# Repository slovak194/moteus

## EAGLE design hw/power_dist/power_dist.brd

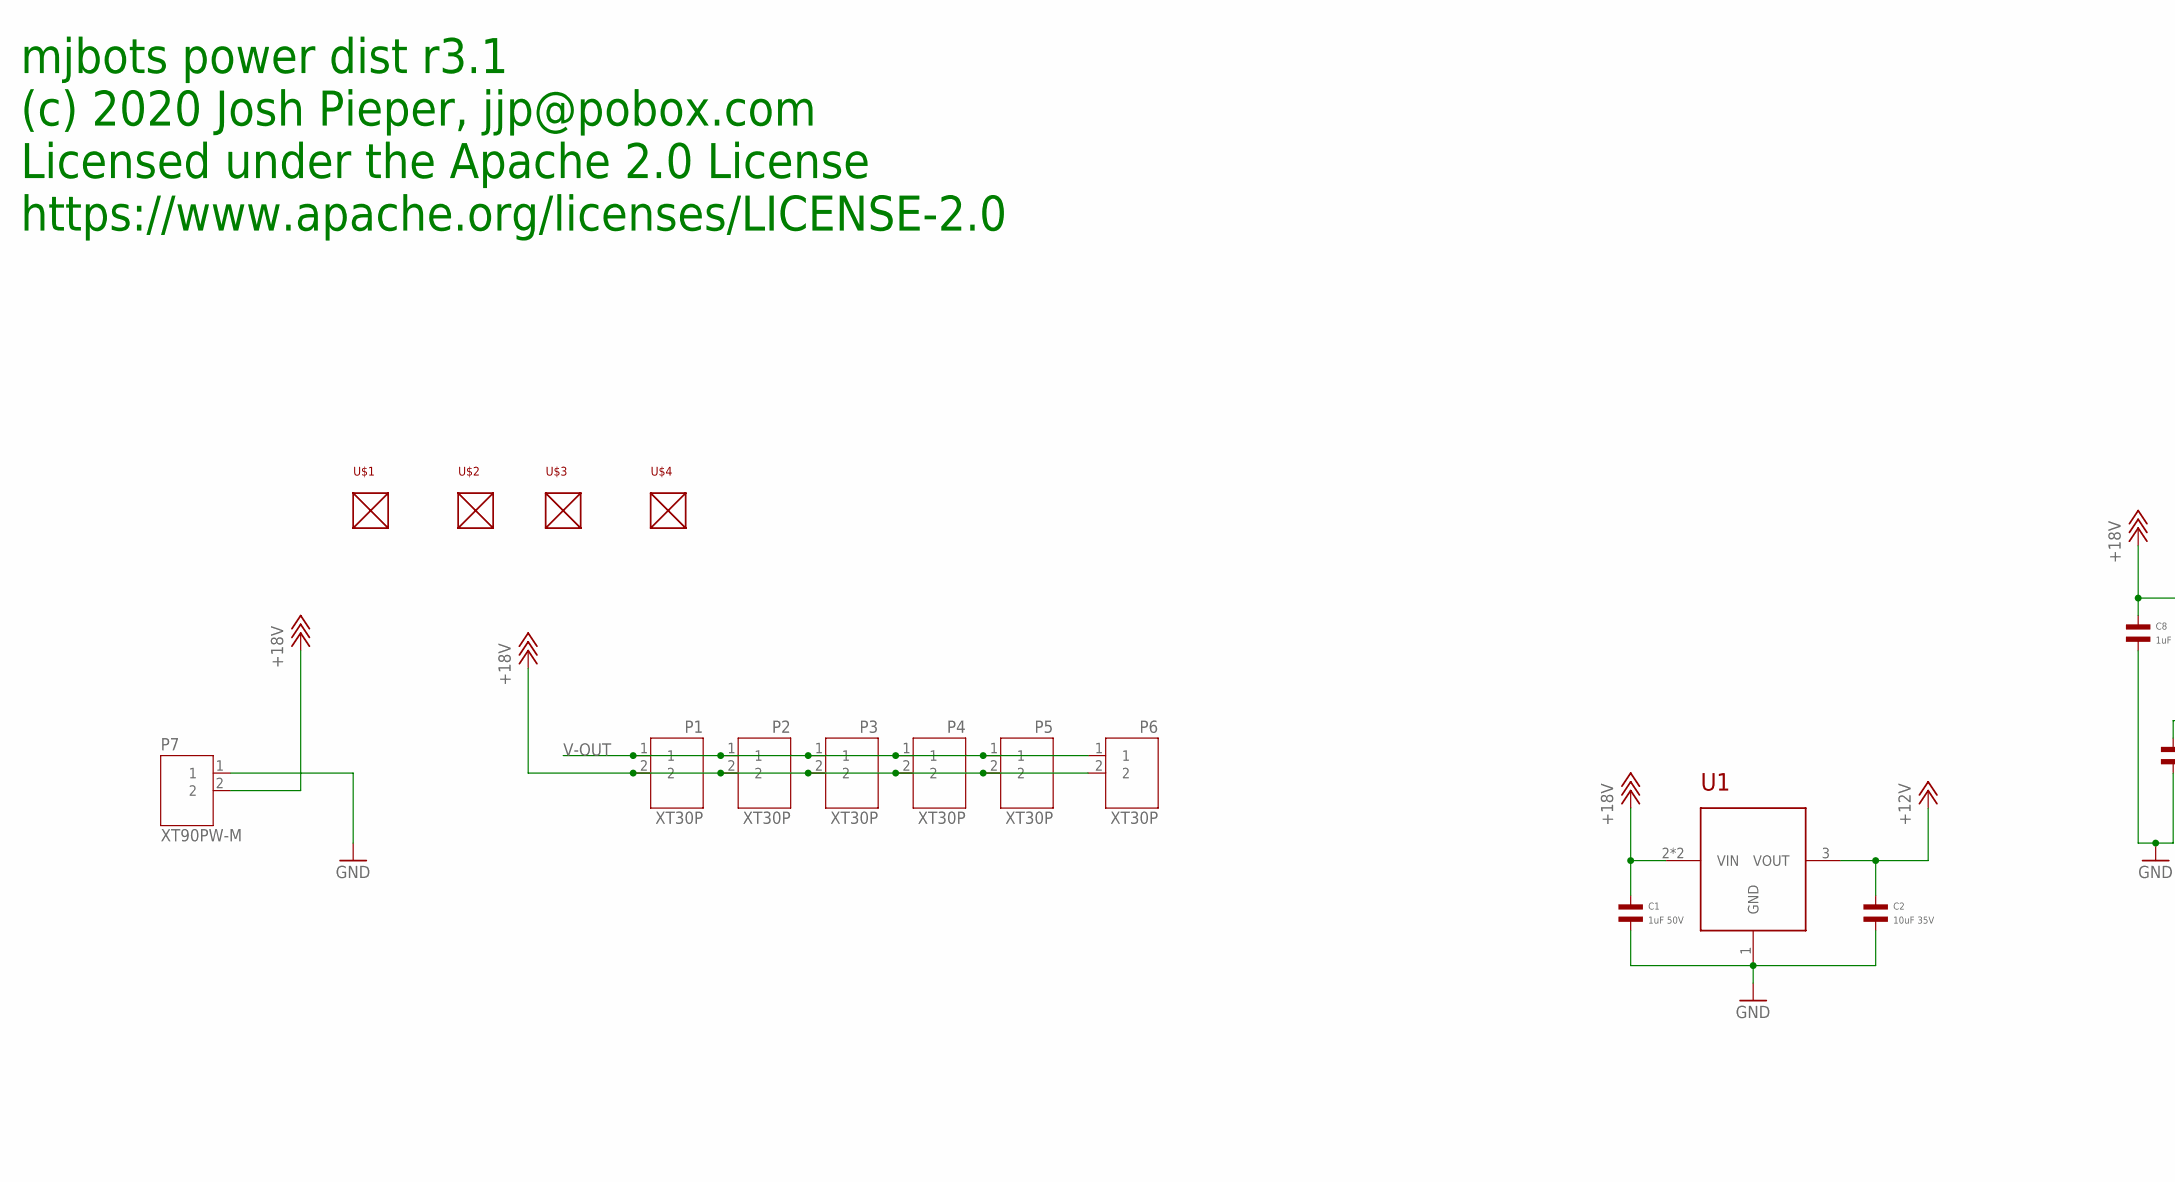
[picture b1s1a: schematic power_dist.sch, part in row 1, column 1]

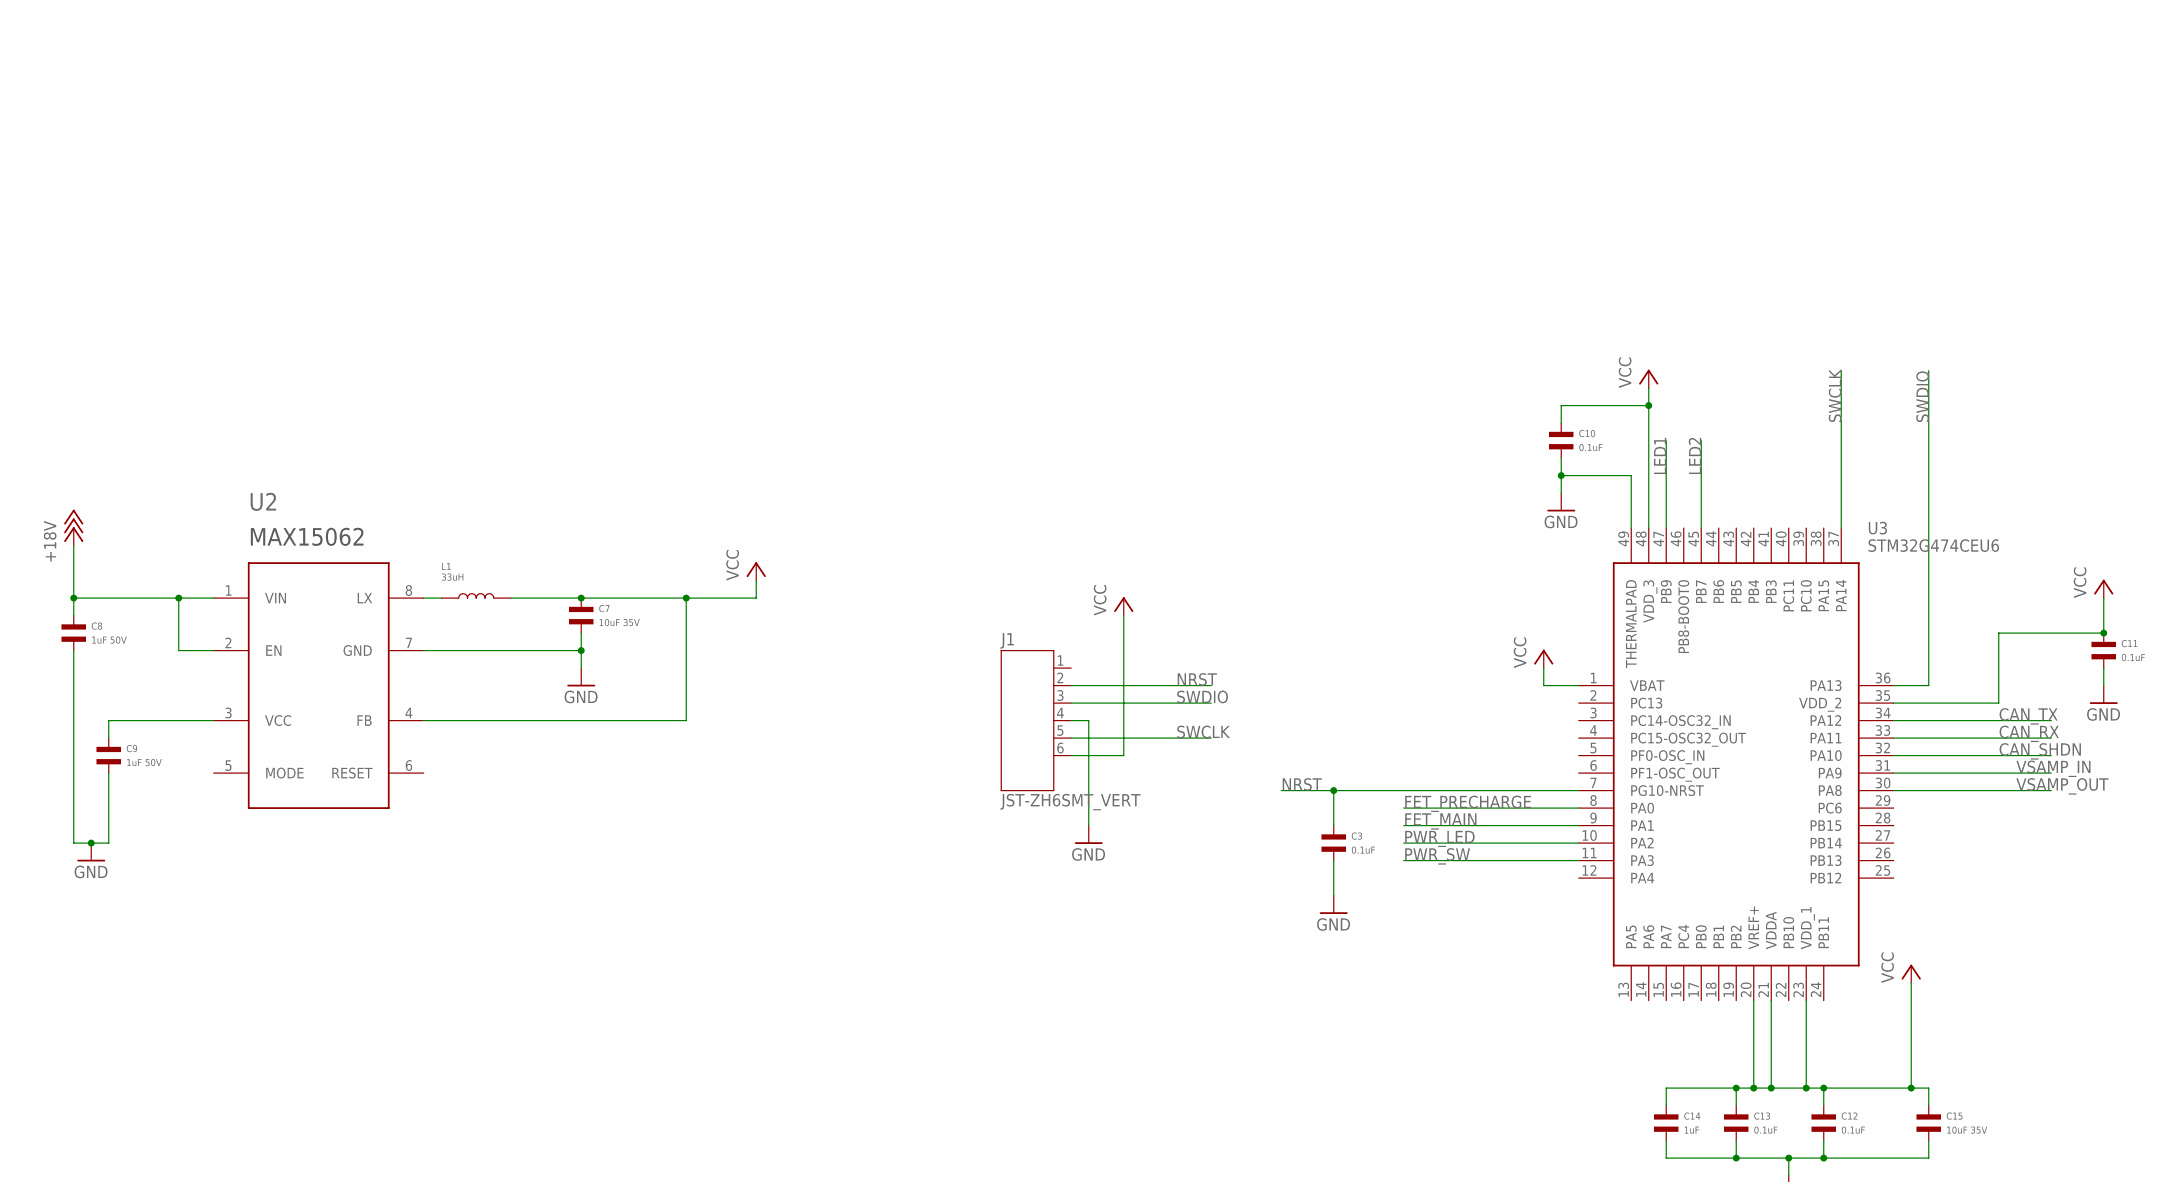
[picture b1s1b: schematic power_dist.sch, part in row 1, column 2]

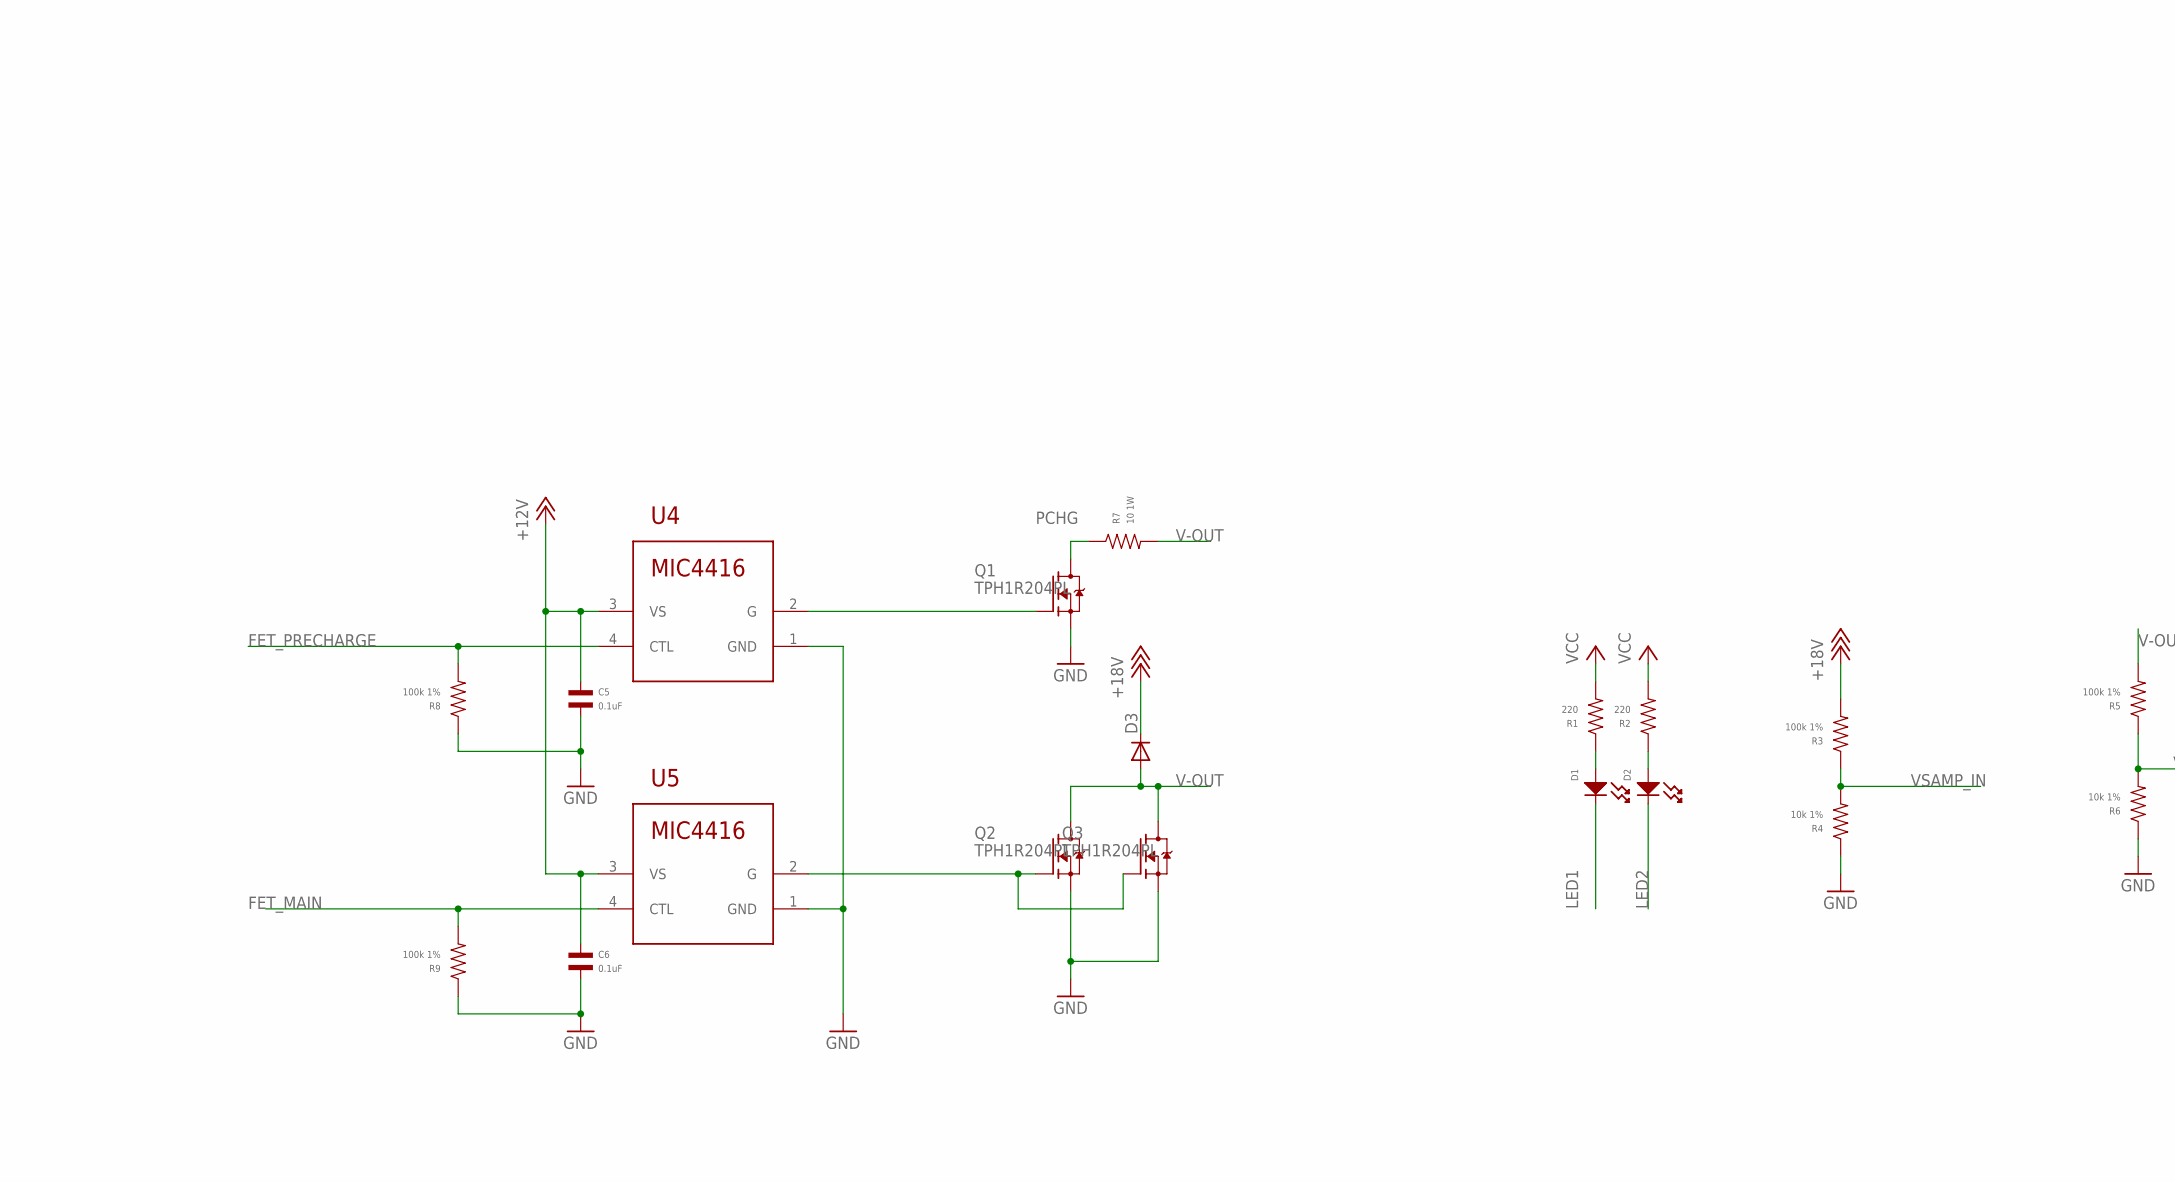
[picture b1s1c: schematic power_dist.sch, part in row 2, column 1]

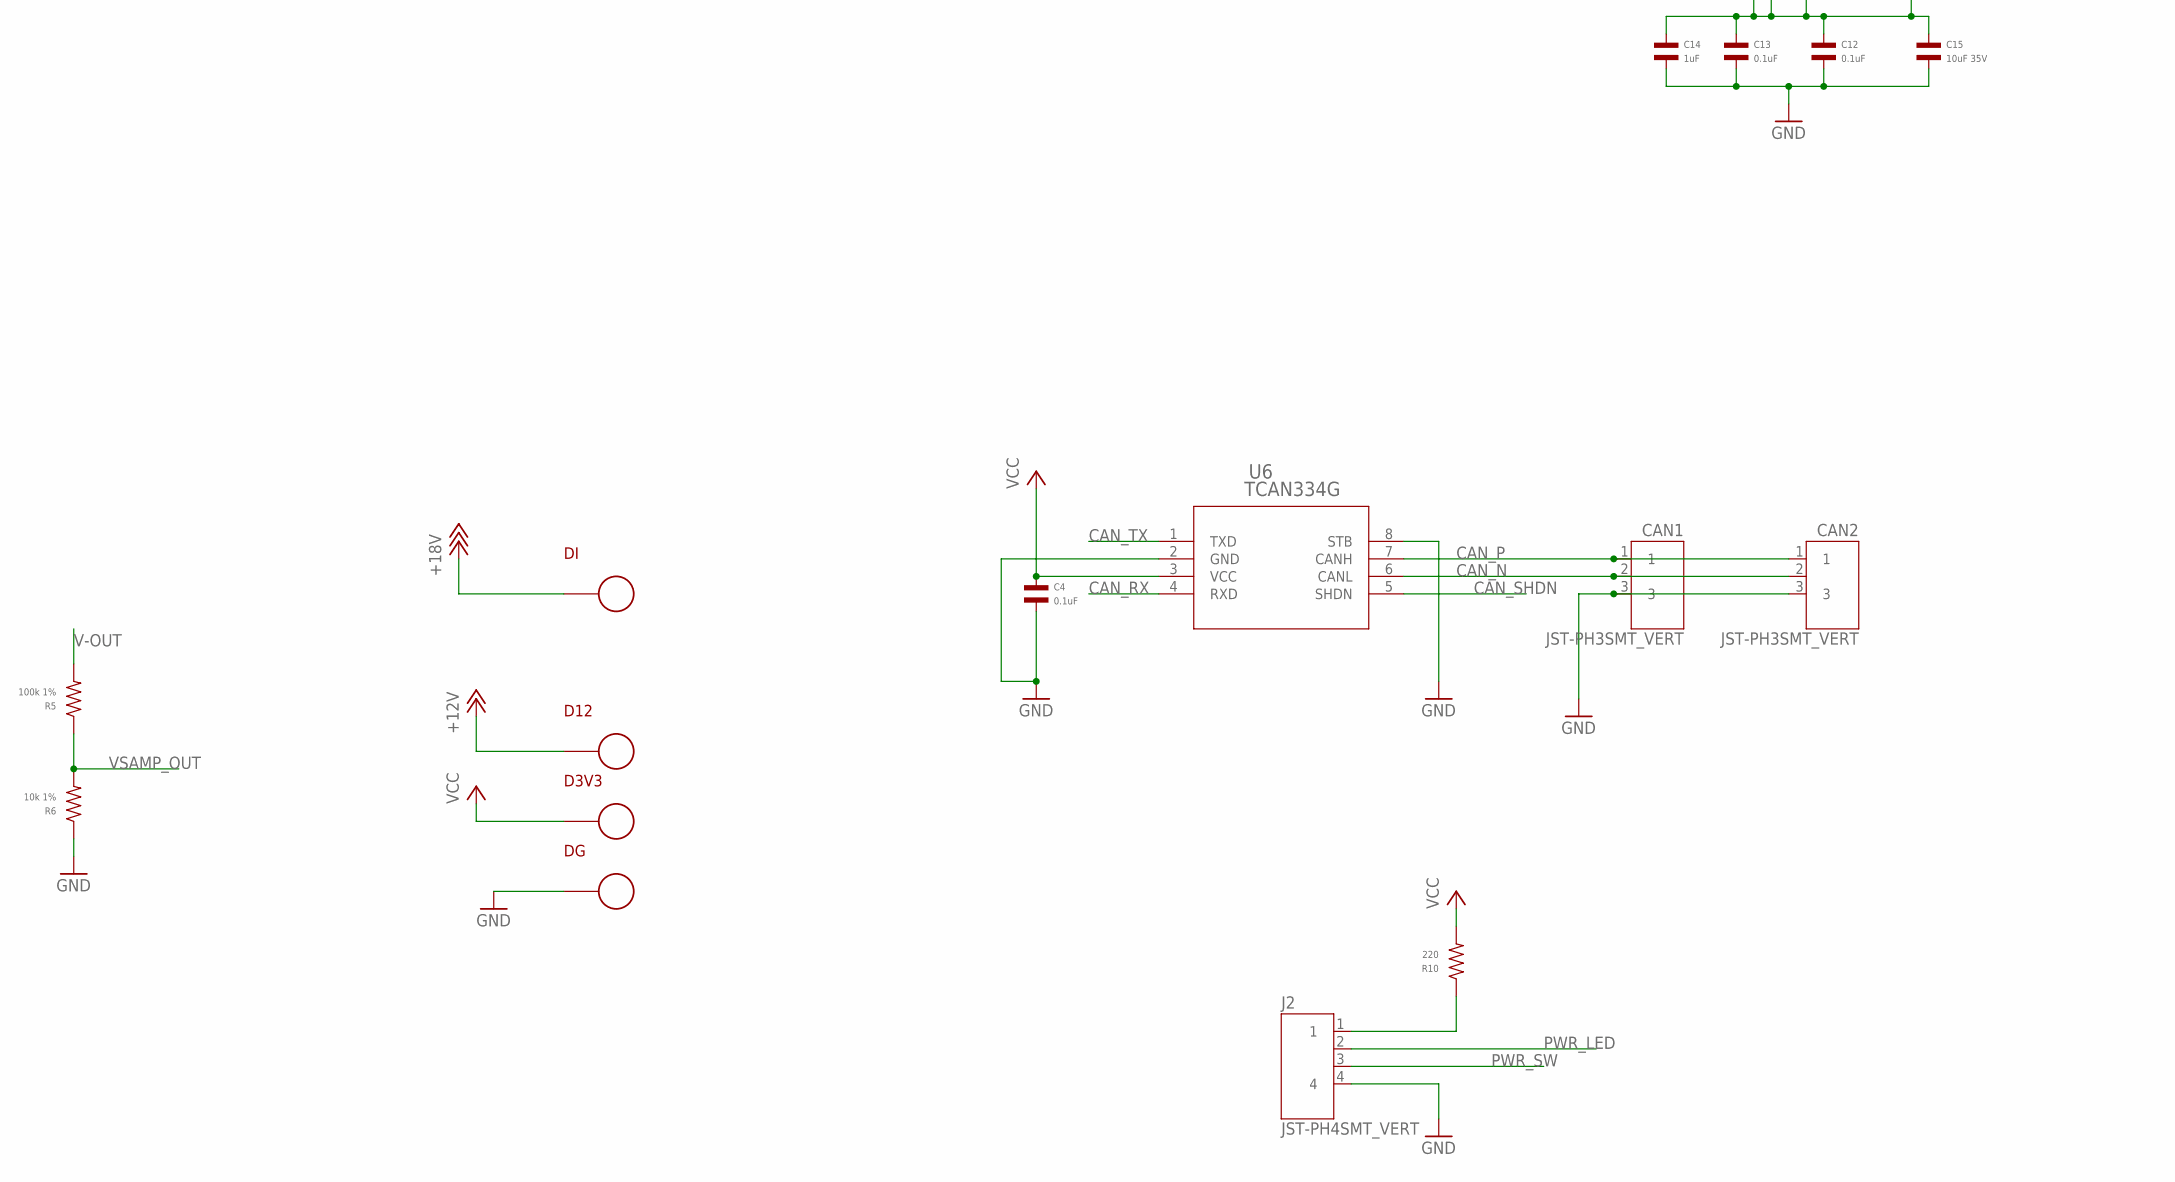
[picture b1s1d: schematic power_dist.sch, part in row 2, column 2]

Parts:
C1, C8, C9: 1uF 50V; C0603; MPN CL10A105KB8NNNC
C2, C7, C15: 10uF 35V; C1206; MPN CGA5L1X7R1V106K160AC
C3, C4, C5, C6, C10, C11, C12, C13: 0.1uF; C0402; MPN MF-CAP-0402-0.1uF
C14: 1uF; C0402; MPN MF-CAP-0402-1uF
CAN1, CAN2: JST-PH3SMT_VERT; JST_B3B_PH-SM4-TB(LF)(SN); MPN B3B-PH-SM4-TB(LF)(SN)
D1, D2: LED_SINGLE-0603; LED0603; MPN MF-LED-0603-RED
D3: DIODE-; DO-214AB; MPN SK510L-TP
D3V3, D12: PAD24AWG_PAD; 24AWG_PAD
DG: PAD24AWG_PAD; 24AWG_PAD
DI: PAD24AWG_PAD; 24AWG_PAD
J1: JST-ZH6SMT_VERT; JST_B6B-ZR-SM4-TF(LF)(SN); MPN B6B-ZR-SM4-TF(LF)(SN)
J2: JST-PH4SMT_VERT; JST_B4B_PH-SM4-TB(LF)(SN); MPN B4B-PH-SM4-TB(LF)(SN)
L1: 33uH; L1210; MPN NLFV32T-330K-EF
P1, P2, P3, P4, P5, P6: XT30P
P7: XT90PW-M
Q1, Q2, Q3: TPH1R204PL; SOP_ADVANCE; MPN TPH1R204PL,L1Q
R1, R2, R10: 220; R0603; MPN MF-RES-0603-220
R3, R5, R8, R9: 100k 1%; R0603; MPN CRCW0603100KFKEA
R4, R6: 10k 1%; R0603; MPN ERJ-3EKF1002V
R7: 10 1W; R1206; MPN HRG3216Q-10R0-D-T1
U1: ZXTR2012Z; SOT89; MPN ZXTR2012Z-13
U2: MAX150628TDFN; 8TDFN; MPN MAX15062AATA+T
U3: STM32G474CEU6; QFN50P700X700X60-49N; MPN STM32G474CEU6
U4, U5: MIC4416; SOT143
U6: TCAN334G; SOIC8; MPN LTC2875IS8
U$1, U$2, U$3, U$4: MOUNT; M2.5MOUNT

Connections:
+12V: C2.P$1, C5.P$1, C6.P$1, D12.P$1, U1.3 (VOUT), U4.3 (VS), U5.3 (VS)
+18V: C1.P$1, C8.P$1, D3.C, DI.P$1, P1.2, P2.2, P3.2, P4.2, P5.2, P6.2, P7.2, R3.P$2, U1.2 (VIN), U1.PAD (VIN), U2.1 (VIN), U2.2 (EN)
CAN_N: CAN1.2, CAN2.2, U6.6 (CANL)
CAN_P: CAN1.1, CAN2.1, U6.7 (CANH)
CAN_RX: U3.33 (PA11), U6.4 (RXD)
CAN_SHDN: U3.32 (PA10), U6.5 (SHDN)
CAN_TX: U3.34 (PA12), U6.1 (TXD)
FET_MAIN: R9.P$2, U3.9 (PA1), U5.4 (CTL)
FET_PRECHARGE: R8.P$2, U3.8 (PA0), U4.4 (CTL)
GND: C1.P$2, C2.P$2, C3.P$2, C4.P$2, C5.P$2, C6.P$2, C7.P$2, C8.P$2, C9.P$2, C10.P$2, C11.P$2, C12.P$2, C13.P$2, C14.P$2, C15.P$2, CAN1.3, CAN2.3, DG.P$1, J1.4, J2.4, P7.1, Q1.1 (S), Q1.2 (S), Q1.3 (S), Q2.1 (S), Q2.2 (S), Q2.3 (S), Q3.1 (S), Q3.2 (S), Q3.3 (S), R4.P$1, R6.P$1, R8.P$1, R9.P$1, U1.1 (GND), U2.7 (GND), U3.49 (THERMALPAD), U4.1 (GND), U5.1 (GND), U6.2 (GND), U6.8 (STB)
LED1: D1.CATHODE, U3.47 (PB9)
LED2: D2.CATHODE, U3.45 (PB7)
LX: L1.P$1, U2.8 (LX)
unnamed: D1.ANODE, R1.P$1
unnamed: J2.1, R10.P$1
unnamed: Q2.4 (G), Q3.4 (G), U5.2 (G)
unnamed: D2.ANODE, R2.P$1
unnamed: Q1.4 (G), U4.2 (G)
unnamed: C9.P$1, U2.3 (VCC)
NRST: C3.P$1, J1.2, U3.7 (PG10-NRST)
PCHG: Q1.5 (D), Q1.6 (D), Q1.7 (D), Q1.8 (D), Q1.PAD (D), R7.P$1
PWR_LED: J2.2, U3.10 (PA2)
PWR_SW: J2.3, U3.11 (PA3)
SWCLK: J1.5, U3.37 (PA14)
SWDIO: J1.3, U3.36 (PA13)
V-OUT: D3.A, P1.1, P2.1, P3.1, P4.1, P5.1, P6.1, Q2.5 (D), Q2.6 (D), Q2.7 (D), Q2.8 (D), Q2.PAD (D), Q3.5 (D), Q3.6 (D), Q3.7 (D), Q3.8 (D), Q3.PAD (D), R5.P$2, R7.P$2
VCC: C4.P$1, C7.P$1, C10.P$1, C11.P$1, C12.P$1, C13.P$1, C14.P$1, C15.P$1, D3V3.P$1, J1.6, L1.P$2, R1.P$2, R2.P$2, R10.P$2, U2.4 (FB), U3.1 (VBAT), U3.20 (VREF+), U3.21 (VDDA), U3.23 (VDD_1), U3.35 (VDD_2), U3.48 (VDD_3), U6.3 (VCC)
VSAMP_IN: R3.P$1, R4.P$2, U3.31 (PA9)
VSAMP_OUT: R5.P$1, R6.P$2, U3.30 (PA8)

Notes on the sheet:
mjbots power dist r3.1 (c) 2020 Josh Pieper, jjp@pobox.com Licensed under the Apache 2.0 License https://www.apache.org/licenses/LICENSE-2.0

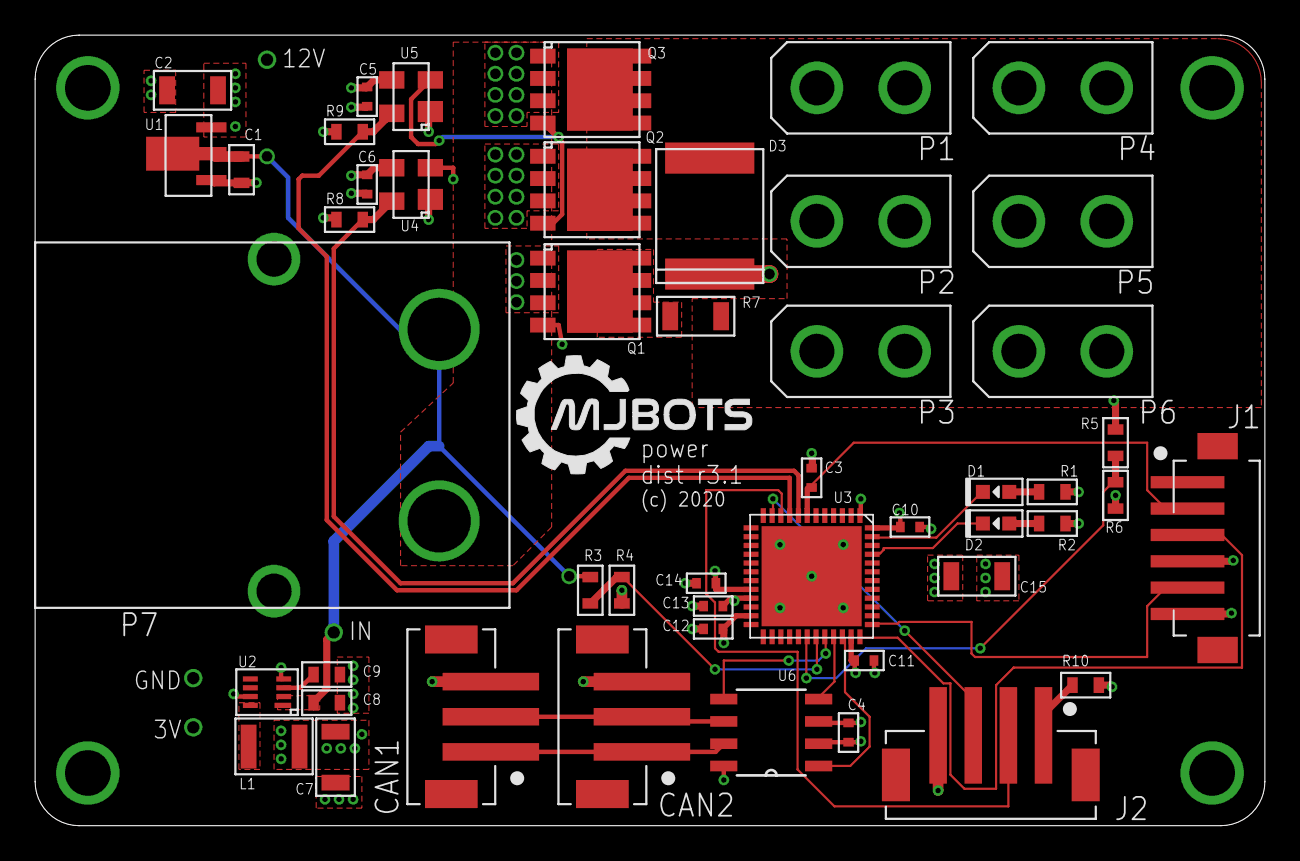
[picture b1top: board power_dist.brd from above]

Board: 4 copper layers, 70.0 x 45.0 mm, 57 parts (0 on the bottom side), 29 nets.

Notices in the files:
hw/as5047_breakout/as5047_breakout.brd:
(c) 2018 jjp@pobox.com
hw/busbar/busbar.brd:
(c) 2019 jjp@pobox.com
